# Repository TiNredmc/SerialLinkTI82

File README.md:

# SerialLinkTI82
SerialLink is the Black-link compatible cable by using RS232 with some trick to make it "TI-link", Compatible with TI-82 and TI-85

# BOM (Can be found cheaply on Aliexpress)
1. x1 PJ-242 2.5mm headphone jack socket (smd)
2. x1 Female DB9 RS232 connector right angle (Through hole mounting)
3. x2 4.7v zener diode smd SOD80C 
4. x2 3.3kOhm resistor smd 0805
5. x1 330Ohm resisitor smd 0805
6. x1 RED_LED smd 1206

# PCB
https://oshpark.com/shared_projects/XNQAIrCI

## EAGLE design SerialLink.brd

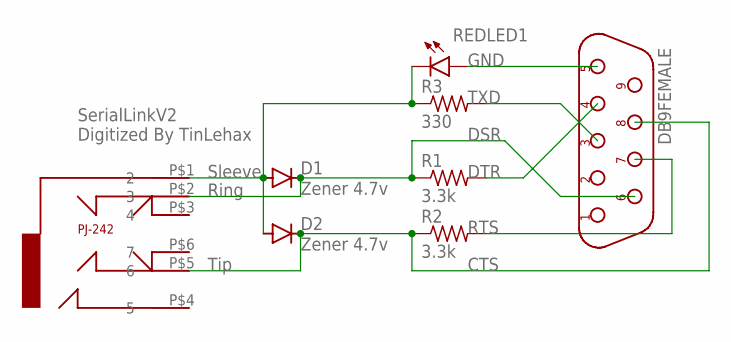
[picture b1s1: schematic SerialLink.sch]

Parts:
D1, D2: Zener 4.7v; SOD80C
DB9FEMALE: DB9F/90; D-09F/90
R1, R2: 3.3k; R0805
R3: 330; R0805
REDLED1: LED1206; LED-1206
U$2: PJ-242

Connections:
unnamed: D1.A, D2.A, R3.1, REDLED1.C, U$2.P$1 (2)
unnamed: D1.C, DB9FEMALE.6, R1.1, U$2.P$2 (3)
unnamed: D2.C, DB9FEMALE.8, R2.1, U$2.P$5 (6)
unnamed: DB9FEMALE.5, REDLED1.A
unnamed: DB9FEMALE.3, R3.2
unnamed: DB9FEMALE.7, R2.2
unnamed: DB9FEMALE.4, R1.2

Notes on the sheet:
Ring
Tip
Sleeve
GND
TXD
DSR
DTR
RTS
CTS
SerialLinkV2 Digitized By TinLehax

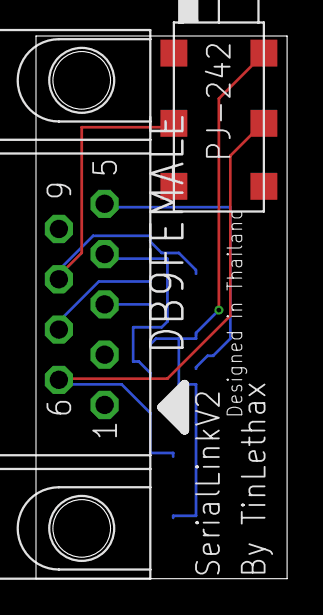
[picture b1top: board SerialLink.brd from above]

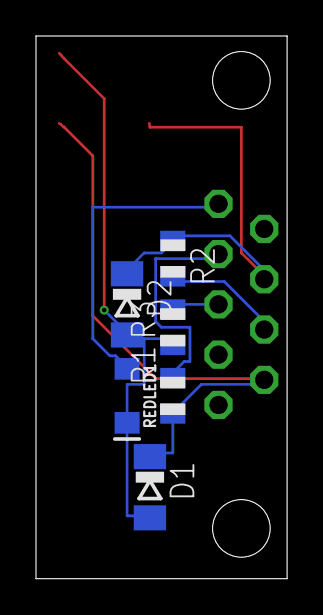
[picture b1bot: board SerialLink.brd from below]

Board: 2 copper layers, 13.9 x 30.1 mm, 8 parts (6 on the bottom side), 7 nets.

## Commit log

2020-03-03 Schematic and board
2020-03-03 added BOM. all parts can be found on aliexpress for cheap
    all parts can be found on aliexpress for cheap
2020-03-03 adde PCB link to OSHpark

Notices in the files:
parts and their libraries:
SparkFun-LED: Licensing: Creative Commons ShareAlike 4.0 International - https://creativecommons.org/licenses/by-sa/4.0
